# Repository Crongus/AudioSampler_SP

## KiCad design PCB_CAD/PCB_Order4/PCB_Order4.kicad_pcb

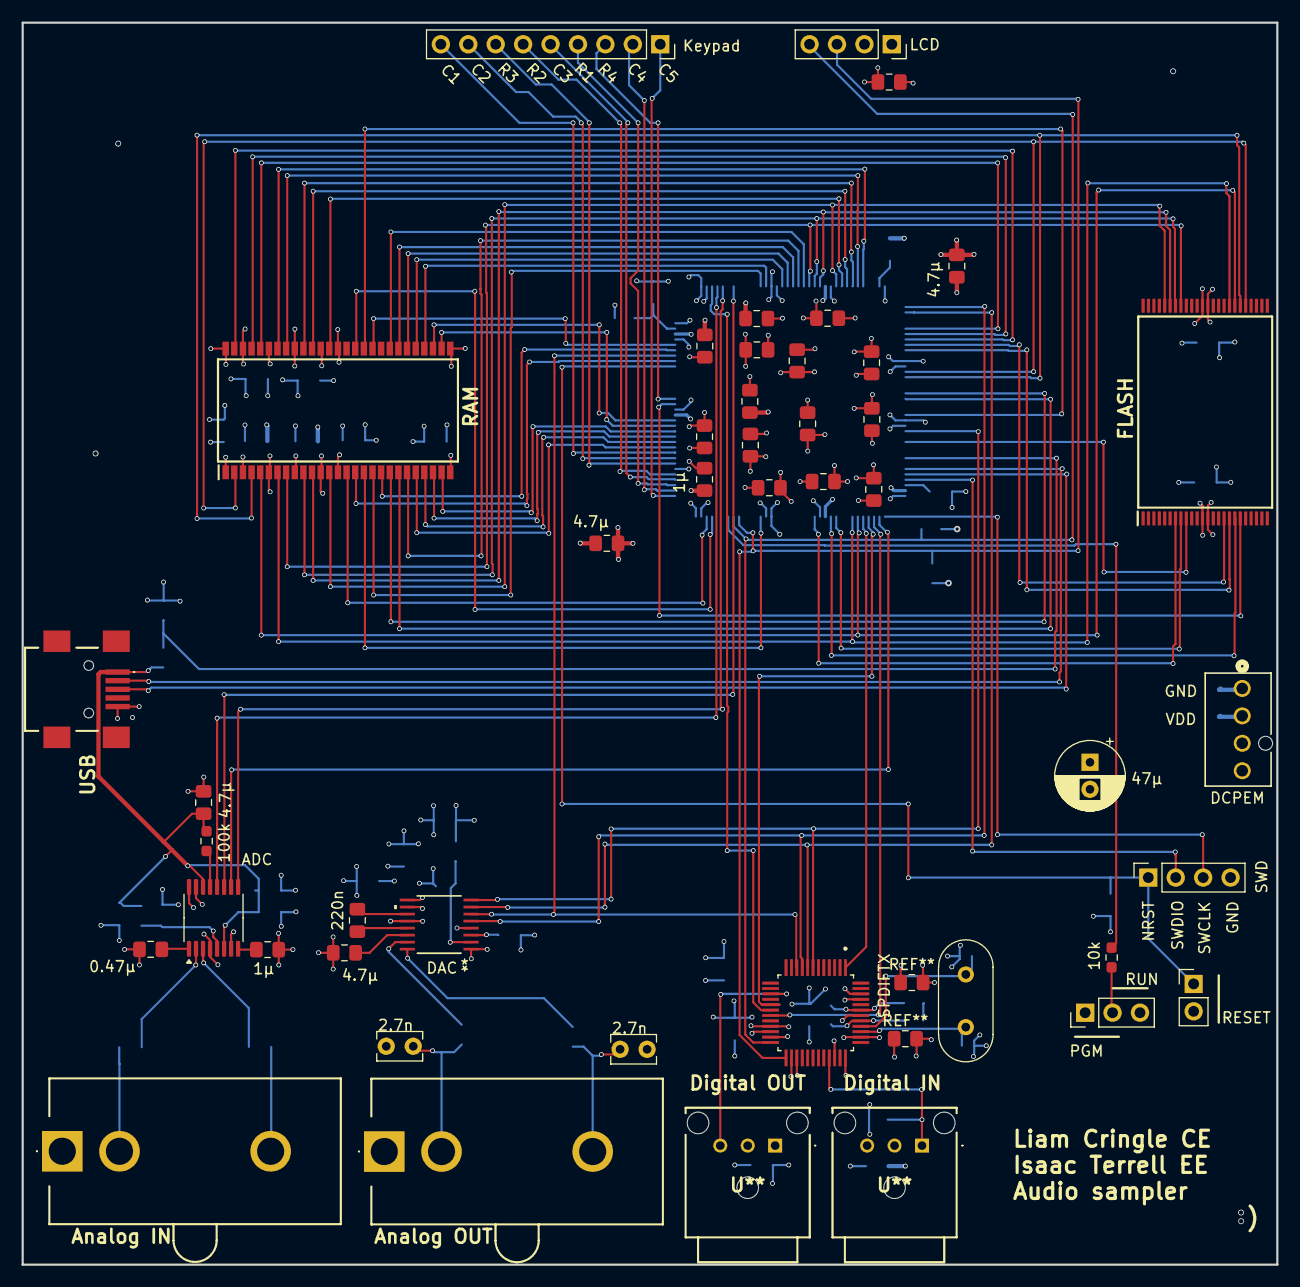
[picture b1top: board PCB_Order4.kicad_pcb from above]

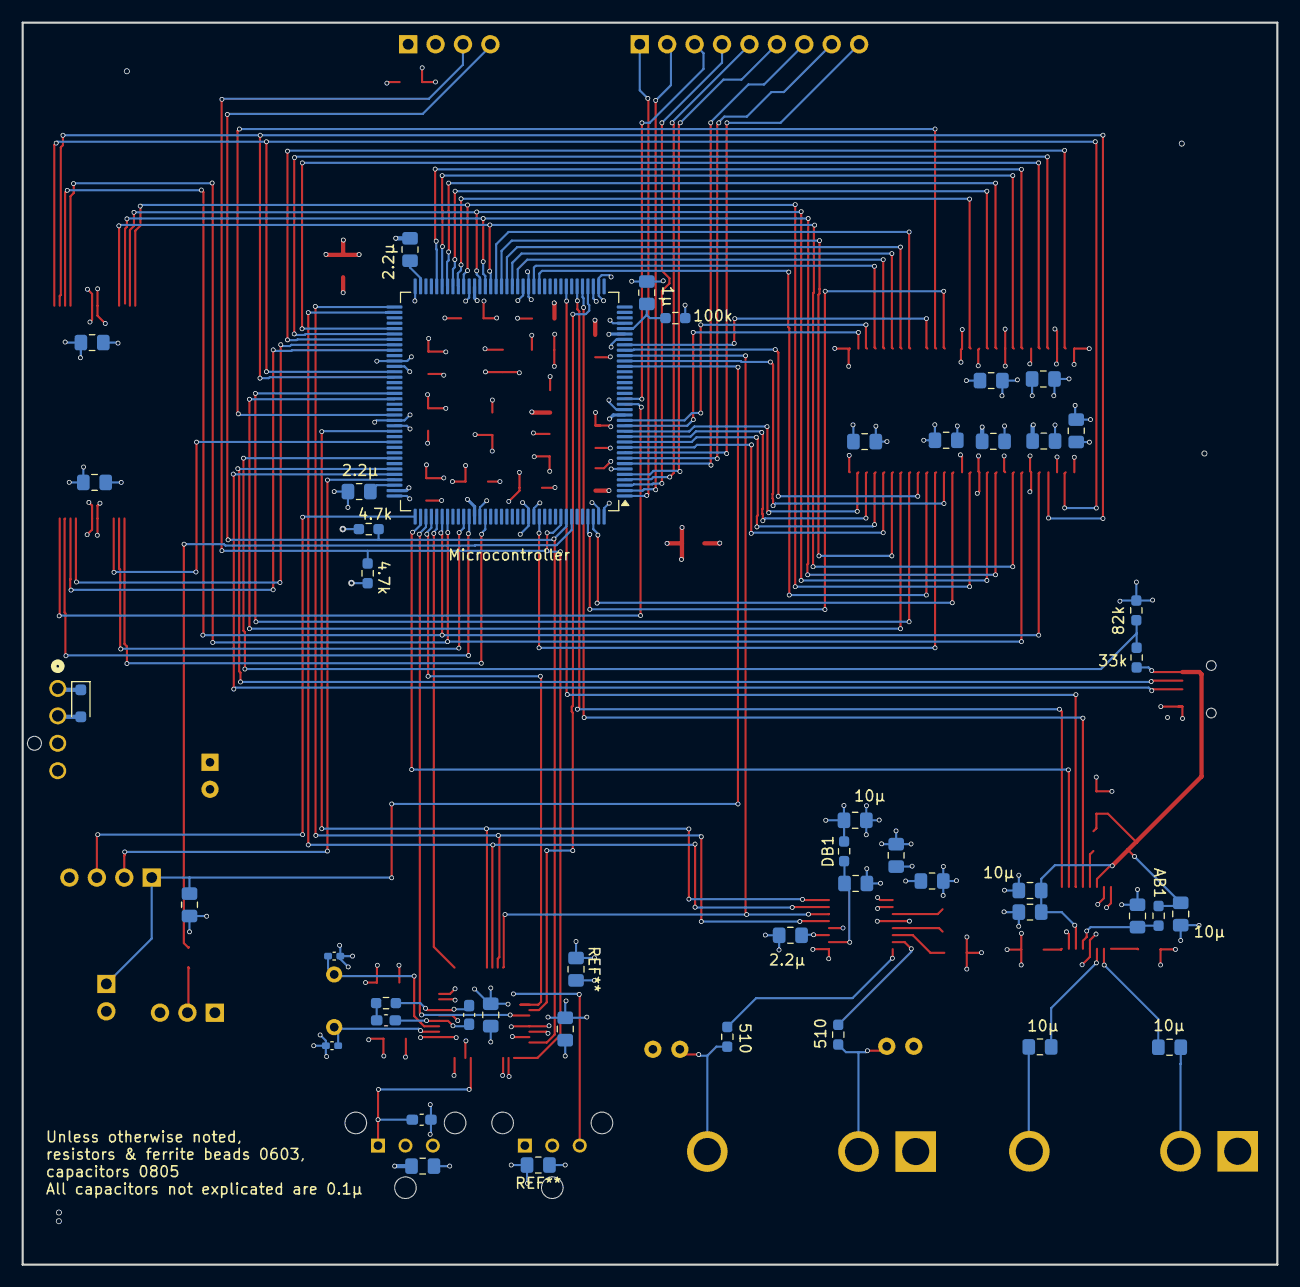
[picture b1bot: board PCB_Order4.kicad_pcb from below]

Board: 4 copper layers, 116.2 x 115.0 mm, 75 parts (32 on the bottom side), 100 nets.

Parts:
AB1: 600; R_0603_1608Metric_Pad0.98x0.95mm_HandSolder
ADC: AK5720VT; TSSOP-16_4.4x5mm_P0.65mm
AR1: 100k; R_0603_1608Metric_Pad0.98x0.95mm_HandSolder
AbC1, AbC2: 10u; C_0805_2012Metric_Pad1.18x1.45mm_HandSolder
AbC3: 4.7u; C_0805_2012Metric_Pad1.18x1.45mm_HandSolder
AcC1: 0.47u; C_0805_2012Metric_Pad1.18x1.45mm_HandSolder
AdbC1, AdbC2: 10u; C_0805_2012Metric_Pad1.18x1.45mm_HandSolder
AnC1, AnC2: 0.1u; C_0805_2012Metric_Pad1.18x1.45mm_HandSolder
Analog IN: FW6190
Analog OUT: FW6190
ArC1: 1u; C_0805_2012Metric_Pad1.18x1.45mm_HandSolder
BC1: 0.1u; C_0805_2012Metric_Pad1.18x1.45mm_HandSolder
DAC: NAU8402WG; TSSOP16_NAU8402_NUV
DB1: 600; R_0603_1608Metric_Pad0.98x0.95mm_HandSolder
DCPEM: 470531000; CONN_SD-47053-001_H10p00_MOL
DacOut_L_decouple1: 2.7n; C_Rect_L4.0mm_W2.5mm_P2.50mm
DacOut_L_res1: 510; R_0603_1608Metric_Pad0.98x0.95mm_HandSolder
DacOut_R_decouple1: 2.7n; C_Rect_L4.0mm_W2.5mm_P2.50mm
DacOut_R_res1: 510; R_0603_1608Metric_Pad0.98x0.95mm_HandSolder
Dac_DigitalSup_noise1, Dac_DigitalSup_noise2: 0.1u; C_0805_2012Metric_Pad1.18x1.45mm_HandSolder
DbC1: 10u; C_0805_2012Metric_Pad1.18x1.45mm_HandSolder
DcC1: 220n; C_0805_2012Metric_Pad1.18x1.45mm_HandSolder
DcC2: 4.7u; C_0805_2012Metric_Pad1.18x1.45mm_HandSolder
DnC1: 0.1u; C_0805_2012Metric_Pad1.18x1.45mm_HandSolder
DrC1: 2.2u; C_0805_2012Metric_Pad1.18x1.45mm_HandSolder
FLASH: TC58BVG1S3HTA00; SOP50P2000X120-48N
FnC1, FnC2: 0.1u; C_0805_2012Metric_Pad1.18x1.45mm_HandSolder
Keypad: PinSocket_1x09_P2.54mm_Vertical
LCD: PinSocket_1x04_P2.54mm_Vertical
LnC1: 0.1u; C_0805_2012Metric_Pad1.18x1.45mm_HandSolder
MR1: 100k; R_0603_1608Metric_Pad0.98x0.95mm_HandSolder
MbC1, MbC2: 4.7u; C_0805_2012Metric_Pad1.18x1.45mm_HandSolder
MbC2#2: 1u; C_0805_2012Metric_Pad1.18x1.45mm_HandSolder
MbC3, MbC4: 2.2u; C_0805_2012Metric_Pad1.18x1.45mm_HandSolder
Microcontroller: STM32H7A3ZITx; LQFP-144_20x20mm_P0.5mm
MnC1, MnC2, MnC3, MnC4, MnC5, MnC6, MnC7, MnC8, MnC9, MnC10, MnC11, MnC12, MnC13: 0.1u; C_0805_2012Metric_Pad1.18x1.45mm_HandSolder
MunC1: 0.1u; C_0805_2012Metric_Pad1.18x1.45mm_HandSolder
MunC2: 1u; C_0805_2012Metric_Pad1.18x1.45mm_HandSolder
PEC3: 47u; CP_Radial_D6.3mm_P2.50mm
RAM: AS4C8M16SA-6TCN; SOP80P1176X120-54N
RESET: PinHeader_1x02_P2.54mm_Vertical
RnC1, RnC2, RnC3, RnC4, RnC5, RnC6, RnC7: 0.1u; C_0805_2012Metric_Pad1.18x1.45mm_HandSolder
SPDIFTX: DIX9211PTR
SR1: 10k; R_0603_1608Metric_Pad0.98x0.95mm_HandSolder
SWD: Conn_01x03_Socket; PinSocket_1x04_P2.54mm_Vertical
U**: FCR684216R
U**#2: FCR684216T
UR1: 33k; R_0603_1608Metric_Pad0.98x0.95mm_HandSolder
UR2: 82k; R_0603_1608Metric_Pad0.98x0.95mm_HandSolder
USB: USB-M26FTR; USBM26FTR

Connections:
/BOOTSW: Microcontroller.138 (BOOT0), SR1.2
/DEBUG_SWCLK: Microcontroller.109 (PA14), SWD.3
/DEBUG_SWDIO: Microcontroller.105 (PA13), SWD.2
/FMC_A0: Microcontroller.10 (PF0), RAM.23 (A0)
/FMC_A1: Microcontroller.11 (PF1), RAM.24 (A1)
/FMC_A2: Microcontroller.12 (PF2), RAM.25 (A2)
/FMC_A3: Microcontroller.13 (PF3), RAM.26 (A3)
/FMC_A4: Microcontroller.14 (PF4), RAM.29 (A4)
/FMC_A5: Microcontroller.15 (PF5), RAM.30 (A5)
/FMC_A6: Microcontroller.50 (PF12), RAM.31 (A6)
/FMC_A7: Microcontroller.53 (PF13), RAM.32 (A7)
/FMC_A8: Microcontroller.54 (PF14), RAM.33 (A8)
/FMC_A9: Microcontroller.55 (PF15), RAM.34 (A9)
/FMC_A10: Microcontroller.56 (PG0), RAM.22 (A10/AP)
/FMC_A11: Microcontroller.57 (PG1), RAM.35 (A11)
/FMC_ALE: FLASH.17 (ALE), Microcontroller.81 (PD12)
/FMC_BA0: Microcontroller.89 (PG4), RAM.20 (BA0)
/FMC_BA1: Microcontroller.90 (PG5), RAM.21 (BA1)
/FMC_CLE: FLASH.16 (CLE), Microcontroller.80 (PD11)
/FMC_D0: FLASH.29 (I/O1), Microcontroller.85 (PD14), RAM.2 (DQ0)
/FMC_D1: FLASH.30 (I/O2), Microcontroller.86 (PD15), RAM.4 (DQ1)
/FMC_D2: FLASH.31 (I/O3), Microcontroller.114 (PD0), RAM.5 (DQ2)
/FMC_D3: FLASH.32 (I/O4), Microcontroller.115 (PD1), RAM.7 (DQ3)
/FMC_D4: FLASH.41 (I/O5), Microcontroller.58 (PE7), RAM.8 (DQ4)
/FMC_D5: FLASH.42 (I/O6), Microcontroller.59 (PE8), RAM.10 (DQ5)
/FMC_D6: FLASH.43 (I/O7), Microcontroller.60 (PE9), RAM.11 (DQ6)
/FMC_D7: FLASH.44 (I/O8), Microcontroller.63 (PE10), RAM.13 (DQ7)
/FMC_D8: Microcontroller.64 (PE11), RAM.42 (DQ8)
/FMC_D9: Microcontroller.65 (PE12), RAM.44 (DQ9)
/FMC_D10: Microcontroller.66 (PE13), RAM.45 (DQ10)
/FMC_D11: Microcontroller.67 (PE14), RAM.47 (DQ11)
/FMC_D12: Microcontroller.68 (PE15), RAM.48 (DQ12)
/FMC_D13: Microcontroller.77 (PD8), RAM.50 (DQ13)
/FMC_D14: Microcontroller.78 (PD9), RAM.51 (DQ14)
/FMC_D15: Microcontroller.79 (PD10), RAM.53 (DQ15)
/FMC_NBL0: Microcontroller.141 (PE0), RAM.39 (UDQM)
/FMC_NBL1: Microcontroller.142 (PE1), RAM.15 (LDQM)
/FMC_NCE: FLASH.9 (~CE), Microcontroller.98 (PC8)
/FMC_NOE: FLASH.8 (~RE), Microcontroller.118 (PD4)
/FMC_NWAIT: FLASH.7 (RY/~BY), Microcontroller.122 (PD6)
/FMC_NWE: FLASH.18 (~WE), Microcontroller.119 (PD5)
/FMC_SDCKE0: Microcontroller.29 (PC3_C), RAM.37 (CKE)
/FMC_SDCLK: Microcontroller.93 (PG8), RAM.38 (CLK)
/FMC_SDNCAS: Microcontroller.132 (PG15), RAM.17 (CAS#)
/FMC_SDNE0: Microcontroller.28 (PC2_C), RAM.19 (CS#)
/FMC_SDNRAS: Microcontroller.49 (PF11), RAM.18 (RAS#)
/FMC_SDNWE: Microcontroller.26 (PC0), RAM.16 (WE#)
/Flash_WP: FLASH.19 (~WP), Microcontroller.18 (PF6)
/I2C1_SCL: LCD.3 (SCL), Microcontroller.136 (PB6), SPDIFTX.25 (MC/SCL)
/I2C1_SDA: LCD.4 (SDA), Microcontroller.137 (PB7), SPDIFTX.24 (MDI/SDA)
/I2S1_CK: ADC.12 (BICK), Microcontroller.41 (PA5)
/I2S1_MCK: ADC.11 (MCLK), Microcontroller.44 (PC4)
/I2S1_SDI: ADC.9 (SDTO), Microcontroller.42 (PA6)
/I2S1_WS: ADC.10 (LRCLK), Microcontroller.110 (PA15)
/I2S2_CK: DAC.7 (BCLK), Microcontroller.74 (PB13), SPDIFTX.8 (MPIO_C1)
/I2S2_MCK: DAC.8 (MCLK), Microcontroller.96 (PC6), SPDIFTX.7 (MPIO_C0)
/I2S2_SDO: DAC.6 (DACIN), Microcontroller.27 (PC1), SPDIFTX.10 (MPIO_C3)
/I2S2_WS: DAC.5 (FS), Microcontroller.73 (PB12), SPDIFTX.9 (MPIO_C2)
/KP_Col1: Keypad.9, Microcontroller.9 (PC15)
/KP_Col2: Keypad.8 (N), Microcontroller.8 (PC14)
/KP_Col3: Keypad.5 (K), Microcontroller.4 (PE5)
/KP_Col4: Keypad.2 (G), Microcontroller.2 (PE3)
/KP_Col5: Keypad.1 (F), Microcontroller.1 (PE2)
/KP_Row1: Keypad.4 (J), Microcontroller.3 (PE4)
/KP_Row2: Keypad.6 (L), Microcontroller.5 (PE6)
/KP_Row3: Keypad.7 (M), Microcontroller.7 (PC13)
/KP_Row4: Keypad.3 (H), Microcontroller.19 (PF7)
/RST_BTN: BC1.1, Microcontroller.25 (NRST), RESET.1, SWD.1
/SPDIFRX_IN0: SPDIFTX.33 (RXIN2), U**.1
/SPDIFTX_OUT: SPDIFTX.15 (MPO0), U**#2.3
/USB_OTG_HS_DM: Microcontroller.103 (PA11), USB.2
/USB_OTG_HS_DP: Microcontroller.104 (PA12), USB.3
/USB_OTG_HS_VBUS: Microcontroller.101 (PA9), UR1.1, UR2.2
GNDD: ADC.4 (VSS), ADC.7 (GSEL), ADC.15 (FSEL), ADC.16 (CKS), AbC1.2, AbC2.2, AbC3.2, AcC1.2, AnC1.1, AnC2.2, Analog IN.1, Analog OUT.1, ArC1.2, BC1.2, DAC.1 (VSSA), DAC.12 (LINEGND), DCPEM.1, DacOut_L_decouple1.2, DacOut_R_decouple1.2, Dac_DigitalSup_noise1.2, Dac_DigitalSup_noise2.2, DbC1.2, DcC2.2, DnC1.1, DrC1.1, FLASH.13 (VSS_1), FLASH.36 (VSS_2), FnC1.1, FnC2.1, LCD.2 (GND), LnC1.1, MbC1.2, MbC2.2, MbC2#2.2, MbC3.2, MbC4.2, Microcontroller.16 (VSS), Microcontroller.31 (VSSA), Microcontroller.38 (VSS), Microcontroller.51 (VSS), Microcontroller.61 (VSS), Microcontroller.83 (VSS), Microcontroller.94 (VSS), Microcontroller.107 (VSS), Microcontroller.120 (VSS), Microcontroller.130 (VSS), MnC1.2, MnC2.2, MnC3.2, MnC4.2, MnC5.2, MnC6.2, MnC7.2, MnC8.2, MnC9.2, MnC10.2, MnC11.1, MnC12.2, MnC13.2, MunC1.2, MunC2.2, PEC3.2, RAM.6 (VSSQ_1), RAM.12 (VSSQ_2), RAM.28 (VSS_1), RAM.41 (VSS_2), RAM.46 (VSSQ_3), RAM.52 (VSSQ_4), RAM.54 (VSS_3), RESET.2, RnC1.2, RnC2.1, RnC3.1, RnC4.1, RnC5.2, RnC6.1, RnC7.1, SPDIFTX.21 (DGND), SPDIFTX.23 (MDO/ADR0), SPDIFTX.26 (MS/ADR1), SPDIFTX.27 (MODE), SPDIFTX.38 (GNDRX), SPDIFTX.41 (AGND), SPDIFTX.45 (RSV1), SPDIFTX.46 (RSV1), SWD.4, U**.2, U**#2.1, UR2.1, USB.5
I2S3_BCK: Microcontroller.111 (PC10), SPDIFTX.19 (BCK)
I2S3_DIN: Microcontroller.112 (PC11), SPDIFTX.17 (DOUT)
I2S3_LRCK: Microcontroller.40 (PA4), SPDIFTX.18 (LRCK)
unnamed: ADC.3 (LIN), AdbC2.2
unnamed: ADC.8 (REGO), ArC1.1
unnamed: ADC.2 (RIN), AdbC1.2
unnamed: AB1.2, ADC.5 (VA), AnC1.2
unnamed: ADC.1 (VCOM), AcC1.1
unnamed: ADC.13 (~PDN), AR1.1
unnamed: AdbC1.1, Analog IN.2
unnamed: AdbC2.1, Analog IN.3
unnamed: DAC.11 (CPCA), DcC1.2
unnamed: DAC.13 (CPCB), DcC1.1
unnamed: DAC.14 (CPOUT), DcC2.1
unnamed: DAC.16 (LLINEOU), DacOut_L_res1.1
unnamed: DAC.15 (RLINEOUT), DacOut_R_res1.1
unnamed: DAC.2 (VDDA), DB1.2, DnC1.2
unnamed: DAC.3 (VREF), DrC1.2
unnamed: Analog OUT.3, DacOut_L_decouple1.1, DacOut_L_res1.2
unnamed: Analog OUT.2, DacOut_R_decouple1.1, DacOut_R_res1.2
unnamed: MbC3.1, Microcontroller.71 (VCAP)
unnamed: MbC4.1, Microcontroller.106 (VCAP)
unnamed: MR1.2, MbC2#2.1, Microcontroller.32 (VREF+)
SPDIF_ERR: Microcontroller.113 (PC12), SPDIFTX.1 (ERROR/INT0)
VDD: DAC.4 (MUTEB), DAC.9 (VDDB), DAC.10 (LINEVDD), DB1.1, DCPEM.2, Dac_DigitalSup_noise1.1, Dac_DigitalSup_noise2.1, DbC1.1, FLASH.12 (VCC_1), FLASH.37 (VCC_2), FnC1.2, FnC2.2, LCD.1 (VCC), LnC1.2, MR1.1, MbC1.1, MbC2.1, Microcontroller.6 (VBAT), Microcontroller.17 (VDD), Microcontroller.30 (VDD), Microcontroller.33 (VDDA), Microcontroller.39 (VDD), Microcontroller.52 (VDD), Microcontroller.62 (VDD), Microcontroller.72 (VDD), Microcontroller.84 (VDD), Microcontroller.95 (VDD33_USB), Microcontroller.108 (VDD), Microcontroller.121 (VDDMMC), Microcontroller.131 (VDD), Microcontroller.143 (PDR_ON), Microcontroller.144 (VDD), MnC1.1, MnC2.1, MnC3.1, MnC4.1, MnC5.1, MnC6.1, MnC7.1, MnC8.1, MnC9.1, MnC10.1, MnC11.2, MnC12.1, MnC13.1, MunC1.1, MunC2.1, PEC3.1, RAM.1 (VDD_1), RAM.3 (VDDQ_1), RAM.9 (VDDQ_2), RAM.14 (VDD_2), RAM.27 (VDD_3), RAM.43 (VDDQ_3), RAM.49 (VDDQ_4), RnC1.1, RnC2.2, RnC3.2, RnC4.2, RnC5.1, RnC6.2, RnC7.2, SPDIFTX.22 (DVDD), SPDIFTX.34 (RST), SPDIFTX.36 (VDDRX), SPDIFTX.42 (VCC), U**.3, U**#2.2
VUSB: AB1.1, ADC.6 (VD), ADC.14 (DIF/TDMI), AR1.2, AbC1.1, AbC2.1, AbC3.1, AnC2.1, UR1.2, USB.1

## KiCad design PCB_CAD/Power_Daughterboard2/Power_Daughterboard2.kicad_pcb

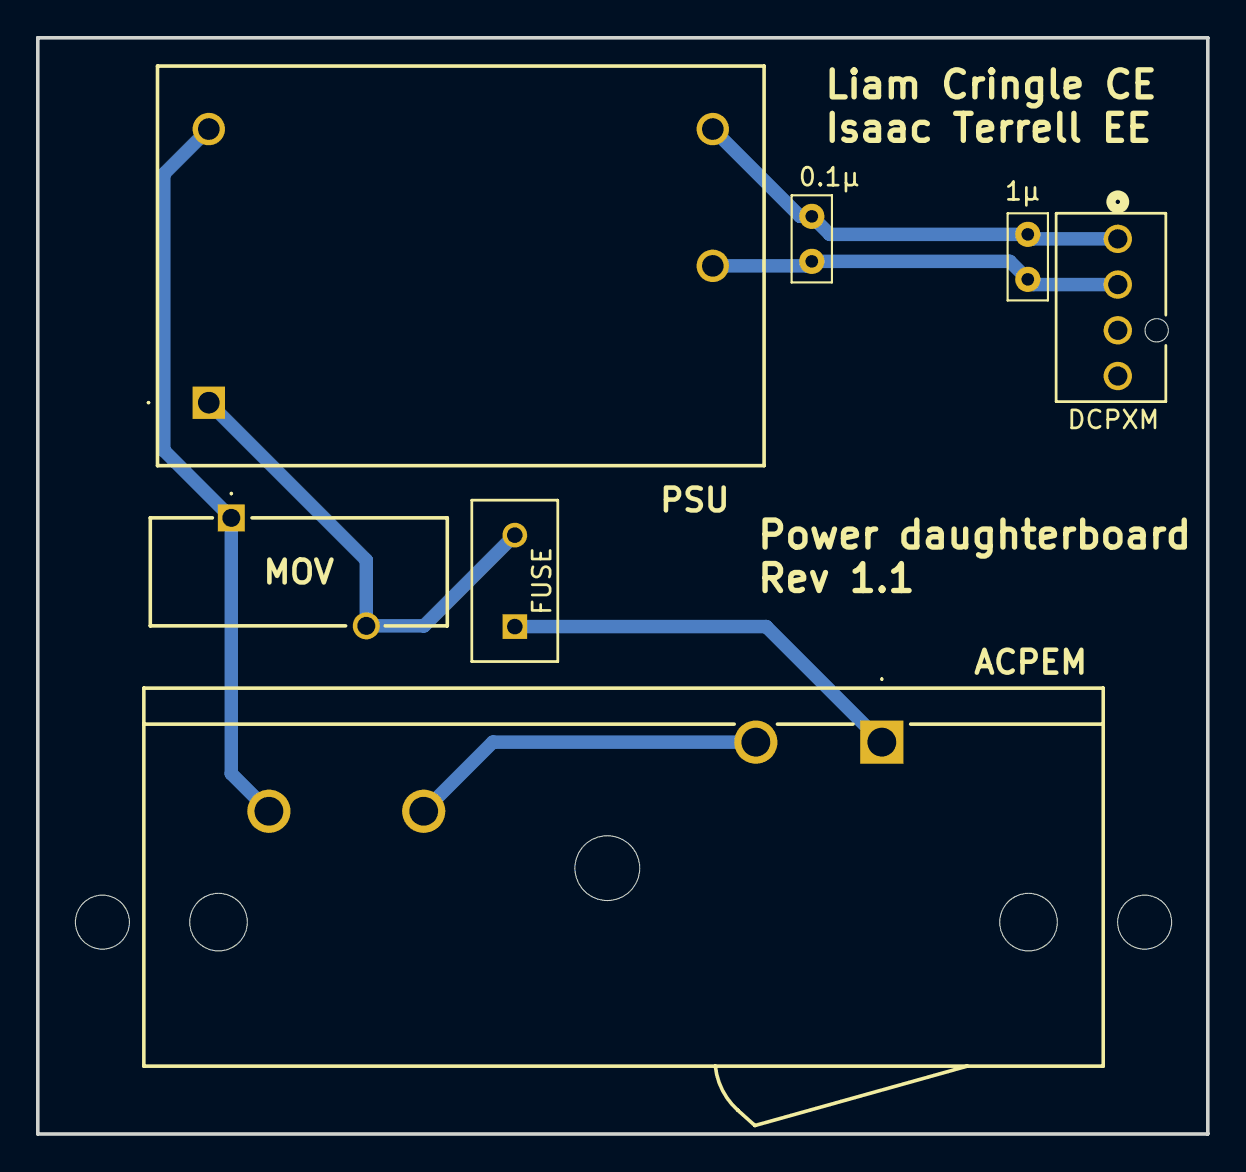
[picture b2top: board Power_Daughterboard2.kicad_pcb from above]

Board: 2 copper layers, 65.0 x 60.9 mm, 7 parts (0 on the bottom side), 6 nets.

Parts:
ACPEM: CMF2113112
C1: 0.1u; C_Rect_L4.6mm_W2.0mm_P2.50mm_MKS02_FKP02
C2: 1u; C_Rect_L4.6mm_W2.0mm_P2.50mm_MKS02_FKP02
DCPXM: 470531000; CONN_SD-47053-001_H10p00_MOL
FUSE: SS-5H-1A-APH; FUSE_SS-5H-1A_EAT
MOV: MOV-14D561KTR; MOV14D561KTR
PSU: HP02S0300WI

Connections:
unnamed: ACPEM.1, FUSE.1
unnamed: ACPEM.2, ACPEM.L1
unnamed: FUSE.2, MOV.2, PSU.1 (AC1)
unnamed: ACPEM.N1, MOV.1, PSU.2 (AC2)
unnamed: C1.1, C2.1, DCPXM.2, PSU.4 (DC+)
unnamed: C1.2, C2.2, DCPXM.1, PSU.3 (DC-)

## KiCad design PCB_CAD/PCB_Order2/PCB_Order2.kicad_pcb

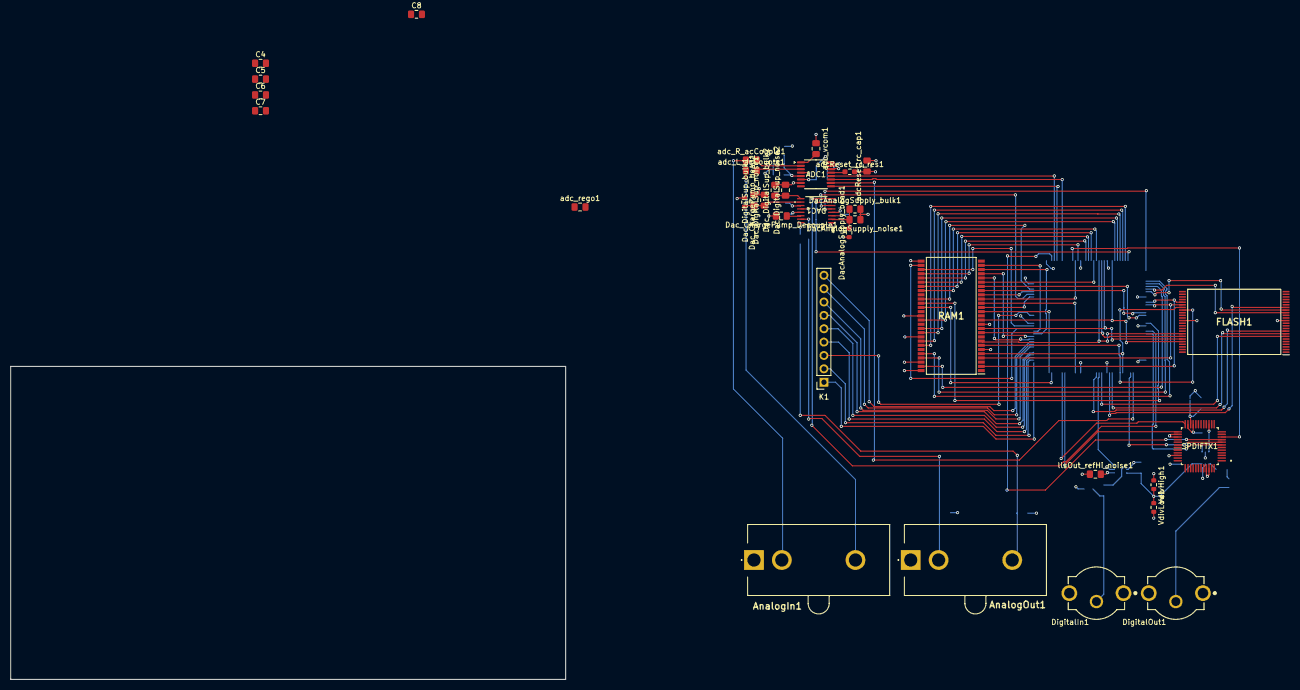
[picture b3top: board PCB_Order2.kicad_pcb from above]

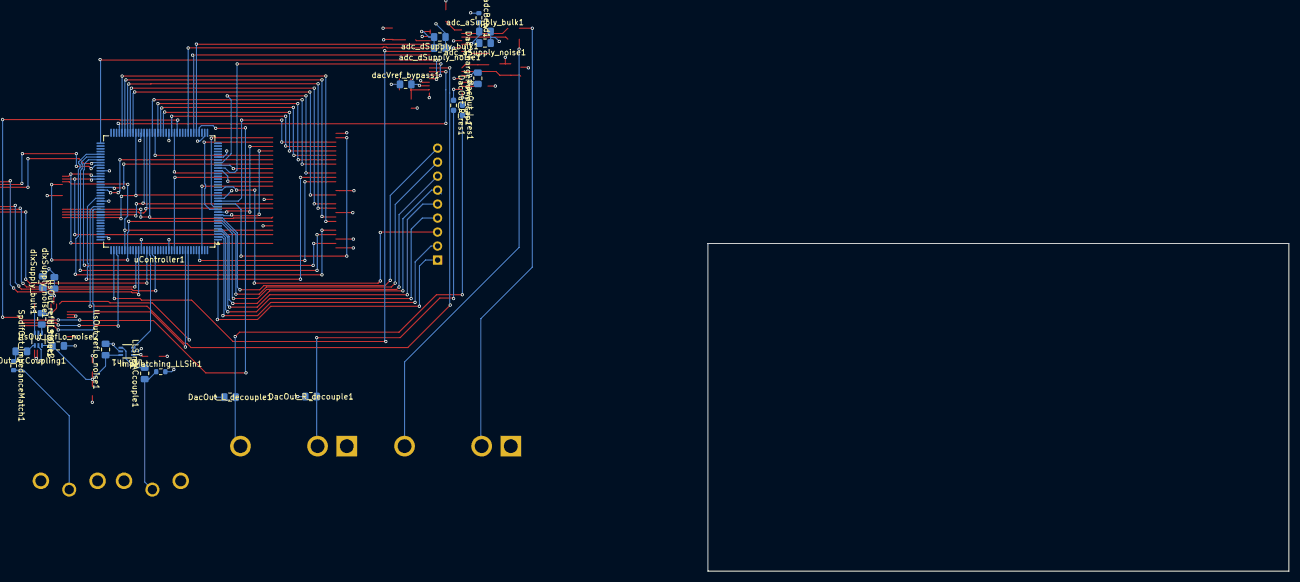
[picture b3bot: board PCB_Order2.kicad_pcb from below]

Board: 4 copper layers, 105.5 x 59.5 mm, 56 parts (23 on the bottom side), 99 nets.

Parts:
ADC1: AK5720VT; TSSOP-16_4.4x5mm_P0.65mm
AnalogIn1: FW6190
AnalogOut1: FW6190
C4, C6: 10uF; C_0805_2012Metric_Pad1.18x1.45mm_HandSolder
C5, C7: 0.1uF; C_0805_2012Metric_Pad1.18x1.45mm_HandSolder
C8: 1uF; C_0805_2012Metric_Pad1.18x1.45mm_HandSolder
DAC1: NAU8402WG; TSSOP16_NAU8402_NUV
DacAnalogSupply_bead1: *TBD*; R_0603_1608Metric
DacAnalogSupply_bulk1: 15u; C_0805_2012Metric_Pad1.18x1.45mm_HandSolder
DacAnalogSupply_noise1: 0.15u; C_0805_2012Metric_Pad1.18x1.45mm_HandSolder
DacOut_L_decouple1: 2.7n; C_0805_2012Metric_Pad1.18x1.45mm_HandSolder
DacOut_L_res1: 500; R_0603_1608Metric_Pad0.98x0.95mm_HandSolder
DacOut_R_decouple1: 2.7n; C_0805_2012Metric_Pad1.18x1.45mm_HandSolder
DacOut_R_res1: 500; R_0603_1608Metric_Pad0.98x0.95mm_HandSolder
Dac_ChargePump_Decouple1: 4.7uF; C_0805_2012Metric_Pad1.18x1.45mm_HandSolder
Dac_ChargePump_bead1: 600; R_0603_1608Metric
Dac_ChargePump_cap1: 220nF; C_0805_2012Metric_Pad1.18x1.45mm_HandSolder
Dac_DigitalSup_bulk1, Dac_DigitalSup_bulk2: 15u; C_0805_2012Metric_Pad1.18x1.45mm_HandSolder
Dac_DigitalSup_noise1, Dac_DigitalSup_noise2: 0.15u; C_0805_2012Metric_Pad1.18x1.45mm_HandSolder
DigitalIn1: RCJ-027; CUI_RCJ-027
DigitalOut1: RCJ-027; CUI_RCJ-027
FLASH1: TC58BVG1S3HTA00; SOP50P2000X120-48N
ImpMatching_LLSin1: 75; R_0603_1608Metric
K1: PinSocket_1x09_P2.54mm_Vertical
LLS In1: SN74AXCH1T45DCKR; DCK6_TEX
LLS Out1: SN74AXCH1T45DCKR; DCK6_TEX
LLSin_ACcouple1: 0.1u; C_0805_2012Metric_Pad1.18x1.45mm_HandSolder
RAM1: AS4C8M16SA-6TCN; SOP80P1176X120-54N
SPDIFTX1: DIX9211PTR
SpdifOut_AcCoupling1: 0.1u; C_0805_2012Metric_Pad1.18x1.45mm_HandSolder
SpdifOut_ImpedanceMatch1: 75; R_0603_1608Metric
VdivHigh1: 8.87k; R_0603_1608Metric
VdivLow1: 2.21k; R_0603_1608Metric
adcBead1: 600; R_0603_1608Metric
adcReset_rc_cap1: 47u; C_0805_2012Metric_Pad1.18x1.45mm_HandSolder
adcReset_rc_res1: 100k; R_0603_1608Metric_Pad0.98x0.95mm_HandSolder
adc_L_acCouple1: 10u; C_0805_2012Metric_Pad1.18x1.45mm_HandSolder
adc_R_acCouple1: 10u; C_0805_2012Metric_Pad1.18x1.45mm_HandSolder
adc_aSupply_bulk1: 15u; C_0805_2012Metric_Pad1.18x1.45mm_HandSolder
adc_aSupply_noise1: 0.15u; C_0805_2012Metric_Pad1.18x1.45mm_HandSolder
adc_dSupply_bulk1: 15u; C_0805_2012Metric_Pad1.18x1.45mm_HandSolder
adc_dSupply_noise1: 0.15u; C_0805_2012Metric_Pad1.18x1.45mm_HandSolder
adc_rego1: 1u; C_0805_2012Metric_Pad1.18x1.45mm_HandSolder
adc_vcom1: 0.47u; C_0805_2012Metric_Pad1.18x1.45mm_HandSolder
dacVref_bypass1: 2.2uF; C_0805_2012Metric_Pad1.18x1.45mm_HandSolder
dixSupply_bulk1: 15u; C_0805_2012Metric_Pad1.18x1.45mm_HandSolder
dixSupply_noise1: 0.15u; C_0805_2012Metric_Pad1.18x1.45mm_HandSolder
llsOut_refHi_noise1, llsOut_refHi_noise2: 0.15u; C_0805_2012Metric_Pad1.18x1.45mm_HandSolder
llsOut_refLo_noise1, llsOut_refLo_noise2: 0.15u; C_0805_2012Metric_Pad1.18x1.45mm_HandSolder
uController1: STM32H7A3ZITx; LQFP-144_20x20mm_P0.5mm

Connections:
/FMC_A0: RAM1.23 (A0), uController1.10 (PF0)
/FMC_A1: RAM1.24 (A1), uController1.11 (PF1)
/FMC_A2: RAM1.25 (A2), uController1.12 (PF2)
/FMC_A3: RAM1.26 (A3), uController1.13 (PF3)
/FMC_A4: RAM1.29 (A4), uController1.14 (PF4)
/FMC_A5: RAM1.30 (A5), uController1.15 (PF5)
/FMC_A6: RAM1.31 (A6), uController1.50 (PF12)
/FMC_A7: RAM1.32 (A7), uController1.53 (PF13)
/FMC_A8: RAM1.33 (A8), uController1.54 (PF14)
/FMC_A9: RAM1.34 (A9), uController1.55 (PF15)
/FMC_A10: RAM1.22 (A10/AP), uController1.56 (PG0)
/FMC_A11: RAM1.35 (A11), uController1.57 (PG1)
/FMC_ALE: FLASH1.17 (ALE), uController1.81 (PD12)
/FMC_BA0: RAM1.20 (BA0), uController1.89 (PG4)
/FMC_BA1: RAM1.21 (BA1), uController1.90 (PG5)
/FMC_CLE: FLASH1.16 (CLE), uController1.80 (PD11)
/FMC_D0: FLASH1.29 (I/O1), RAM1.2 (DQ0), uController1.85 (PD14)
/FMC_D1: FLASH1.30 (I/O2), RAM1.4 (DQ1), uController1.86 (PD15)
/FMC_D2: FLASH1.31 (I/O3), RAM1.5 (DQ2), uController1.114 (PD0)
/FMC_D3: FLASH1.32 (I/O4), RAM1.7 (DQ3), uController1.115 (PD1)
/FMC_D4: FLASH1.41 (I/O5), RAM1.8 (DQ4), uController1.58 (PE7)
/FMC_D5: FLASH1.42 (I/O6), RAM1.10 (DQ5), uController1.59 (PE8)
/FMC_D6: FLASH1.43 (I/O7), RAM1.11 (DQ6), uController1.60 (PE9)
/FMC_D7: FLASH1.44 (I/O8), RAM1.13 (DQ7), uController1.63 (PE10)
/FMC_D8: RAM1.42 (DQ8), uController1.64 (PE11)
/FMC_D9: RAM1.44 (DQ9), uController1.65 (PE12)
/FMC_D10: RAM1.45 (DQ10), uController1.66 (PE13)
/FMC_D11: RAM1.47 (DQ11), uController1.67 (PE14)
/FMC_D12: RAM1.48 (DQ12), uController1.68 (PE15)
/FMC_D13: RAM1.50 (DQ13), uController1.77 (PD8)
/FMC_D14: RAM1.51 (DQ14), uController1.78 (PD9)
/FMC_D15: RAM1.53 (DQ15), uController1.79 (PD10)
/FMC_NBL0: RAM1.39 (UDQM), uController1.141 (PE0)
/FMC_NBL1: RAM1.15 (LDQM), uController1.142 (PE1)
/FMC_NCE: FLASH1.9 (~CE), uController1.124 (PG9)
/FMC_NOE: FLASH1.8 (~RE), uController1.118 (PD4)
/FMC_NWAIT: FLASH1.7 (RY/~BY), uController1.122 (PD6)
/FMC_NWE: FLASH1.18 (~WE), uController1.119 (PD5)
/FMC_SDCKE0: RAM1.37 (CKE), uController1.29 (PC3_C)
/FMC_SDCLK: RAM1.38 (CLK), uController1.93 (PG8)
/FMC_SDNCAS: RAM1.17 (CAS#), uController1.132 (PG15)
/FMC_SDNE0: RAM1.19 (CS#), uController1.28 (PC2_C)
/FMC_SDNRAS: RAM1.18 (RAS#), uController1.49 (PF11)
/FMC_SDNWE: RAM1.16 (WE#), uController1.26 (PC0)
/Flash_WP: FLASH1.19 (~WP), uController1.18 (PF6)
/I2C1_SCL: SPDIFTX1.25 (MC/SCL), uController1.136 (PB6)
/I2C1_SDA: SPDIFTX1.24 (MDI/SDA), uController1.137 (PB7)
/I2S1_CK: ADC1.12 (BICK), uController1.41 (PA5)
/I2S1_MCK: ADC1.11 (MCLK), uController1.44 (PC4)
/I2S1_SDI: ADC1.9 (SDTO), uController1.42 (PA6)
/I2S1_WS: ADC1.10 (LRCLK), uController1.110 (PA15)
/I2S2_CK: DAC1.7 (BCLK), uController1.69 (PB10)
/I2S2_MCK: DAC1.8 (MCLK), uController1.96 (PC6)
/I2S2_SDO: DAC1.6 (DACIN), uController1.27 (PC1)
/I2S2_WS: DAC1.5 (FS), uController1.73 (PB12)
/I2S3_CK: SPDIFTX1.8 (MPIO_C1), uController1.111 (PC10)
/I2S3_MCK: SPDIFTX1.7 (MPIO_C0), uController1.97 (PC7)
/I2S3_SDO: SPDIFTX1.10 (MPIO_C3), uController1.48 (PB2)
/I2S3_WS: SPDIFTX1.9 (MPIO_C2), uController1.40 (PA4)
/KP_Col1: K1.9, uController1.9 (PC15)
/KP_Col2: K1.8 (N), uController1.8 (PC14)
/KP_Col3: K1.5 (K), uController1.4 (PE5)
/KP_Col4: K1.2 (G), uController1.2 (PE3)
/KP_Col5: K1.1 (F), uController1.1 (PE2)
/KP_Row1: K1.4 (J), uController1.3 (PE4)
/KP_Row2: K1.6 (L), uController1.5 (PE6)
/KP_Row3: K1.7 (M), uController1.7 (PC13)
/KP_Row4: K1.3 (H), uController1.19 (PF7)
/SPDIFRX_IN0: LLS In1.3 (A), uController1.123 (PD7)
/SPDIFTX_OUT: LLS Out1.3 (A), SPDIFTX1.15 (MPO0)
GNDA: ADC1.4 (VSS), AnalogIn1.1, AnalogOut1.1, C4.2, C5.1, DAC1.1 (VSSA), DAC1.12 (LINEGND), uController1.31 (VSSA)
GNDD: ADC1.7 (GSEL), ADC1.15 (FSEL), ADC1.16 (CKS), C6.2, C7.1, C8.2, DacAnalogSupply_bulk1.2, DacAnalogSupply_noise1.1, DacOut_L_decouple1.2, DacOut_R_decouple1.2, Dac_ChargePump_Decouple1.2, Dac_DigitalSup_bulk1.2, Dac_DigitalSup_bulk2.2, Dac_DigitalSup_noise1.2, Dac_DigitalSup_noise2.2, DigitalIn1.1A (1), DigitalOut1.1A (1), FLASH1.13 (VSS_1), FLASH1.36 (VSS_2), ImpMatching_LLSin1.2, LLS In1.2 (GND), LLS In1.5 (DIR), LLS Out1.2 (GND), RAM1.6 (VSSQ_1), RAM1.12 (VSSQ_2), RAM1.28 (VSS_1), RAM1.41 (VSS_2), RAM1.46 (VSSQ_3), RAM1.52 (VSSQ_4), RAM1.54 (VSS_3), SPDIFTX1.21 (DGND), SPDIFTX1.23 (MDO/ADR0), SPDIFTX1.26 (MS/ADR1), SPDIFTX1.27 (MODE), SPDIFTX1.45 (RSV1), SPDIFTX1.46 (RSV1), VdivLow1.2, adcReset_rc_cap1.2, adc_aSupply_bulk1.2, adc_aSupply_noise1.1, adc_dSupply_bulk1.2, adc_dSupply_noise1.2, adc_rego1.2, adc_vcom1.1, dacVref_bypass1.1, dixSupply_bulk1.2, dixSupply_noise1.2, llsOut_refHi_noise1.1, llsOut_refHi_noise2.1, llsOut_refLo_noise1.2, llsOut_refLo_noise2.2, uController1.16 (VSS), uController1.38 (VSS), uController1.51 (VSS), uController1.61 (VSS), uController1.83 (VSS), uController1.94 (VSS), uController1.107 (VSS), uController1.120 (VSS), uController1.130 (VSS)
unnamed: ADC1.3 (LIN), adc_L_acCouple1.2
unnamed: ADC1.8 (REGO), C8.1, adc_rego1.1
unnamed: ADC1.2 (RIN), adc_R_acCouple1.2
unnamed: ADC1.5 (VA), adcBead1.2, adc_aSupply_bulk1.1, adc_aSupply_noise1.2
unnamed: ADC1.1 (VCOM), adc_vcom1.2
unnamed: ADC1.13 (~PDN), adcReset_rc_res1.1
unnamed: AnalogIn1.2, adc_R_acCouple1.1
unnamed: AnalogIn1.3, adc_L_acCouple1.1
unnamed: AnalogOut1.2, DacOut_R_decouple1.1, DacOut_R_res1.2
unnamed: AnalogOut1.3, DacOut_L_decouple1.1, DacOut_L_res1.2
unnamed: DAC1.11 (CPCA), Dac_ChargePump_cap1.2
unnamed: DAC1.13 (CPCB), Dac_ChargePump_cap1.1
unnamed: DAC1.14 (CPOUT), Dac_ChargePump_Decouple1.1
unnamed: DAC1.10 (LINEVDD), Dac_ChargePump_bead1.2, Dac_DigitalSup_bulk1.1, Dac_DigitalSup_noise1.1
unnamed: DAC1.16 (LLINEOU), DacOut_L_res1.1
unnamed: DAC1.15 (RLINEOUT), DacOut_R_res1.1
unnamed: DAC1.2 (VDDA), DacAnalogSupply_bead1.2, DacAnalogSupply_bulk1.1, DacAnalogSupply_noise1.2
unnamed: DAC1.3 (VREF), dacVref_bypass1.2
unnamed: DigitalIn1.2, ImpMatching_LLSin1.1, LLSin_ACcouple1.1
unnamed: DigitalOut1.2, SpdifOut_ImpedanceMatch1.2
unnamed: LLS In1.4 (B), LLSin_ACcouple1.2
unnamed: LLS Out1.4 (B), SpdifOut_AcCoupling1.1
unnamed: SpdifOut_AcCoupling1.2, SpdifOut_ImpedanceMatch1.1
VCCQ: RAM1.3 (VDDQ_1), RAM1.9 (VDDQ_2), RAM1.43 (VDDQ_3), RAM1.49 (VDDQ_4)
VDD: ADC1.6 (VD), ADC1.14 (DIF/TDMI), C6.1, C7.2, DAC1.4 (MUTEB), DAC1.9 (VDDB), DacAnalogSupply_bead1.1, Dac_ChargePump_bead1.1, Dac_DigitalSup_bulk2.1, Dac_DigitalSup_noise2.1, FLASH1.12 (VCC_1), FLASH1.37 (VCC_2), LLS Out1.1 (VCCA), LLS Out1.5 (DIR), RAM1.1 (VDD_1), RAM1.14 (VDD_2), RAM1.27 (VDD_3), SPDIFTX1.22 (DVDD), SPDIFTX1.34 (RST), VdivHigh1.1, adcBead1.1, adcReset_rc_cap1.1, adcReset_rc_res1.2, adc_dSupply_bulk1.1, adc_dSupply_noise1.1, dixSupply_bulk1.1, dixSupply_noise1.1, llsOut_refHi_noise2.2
VDDA: C4.1, C5.2, LLS In1.1 (VCCA), llsOut_refHi_noise1.2
VDD_DIV: LLS In1.6 (VCCB), LLS Out1.6 (VCCB), VdivHigh1.2, VdivLow1.1, llsOut_refLo_noise1.1, llsOut_refLo_noise2.1

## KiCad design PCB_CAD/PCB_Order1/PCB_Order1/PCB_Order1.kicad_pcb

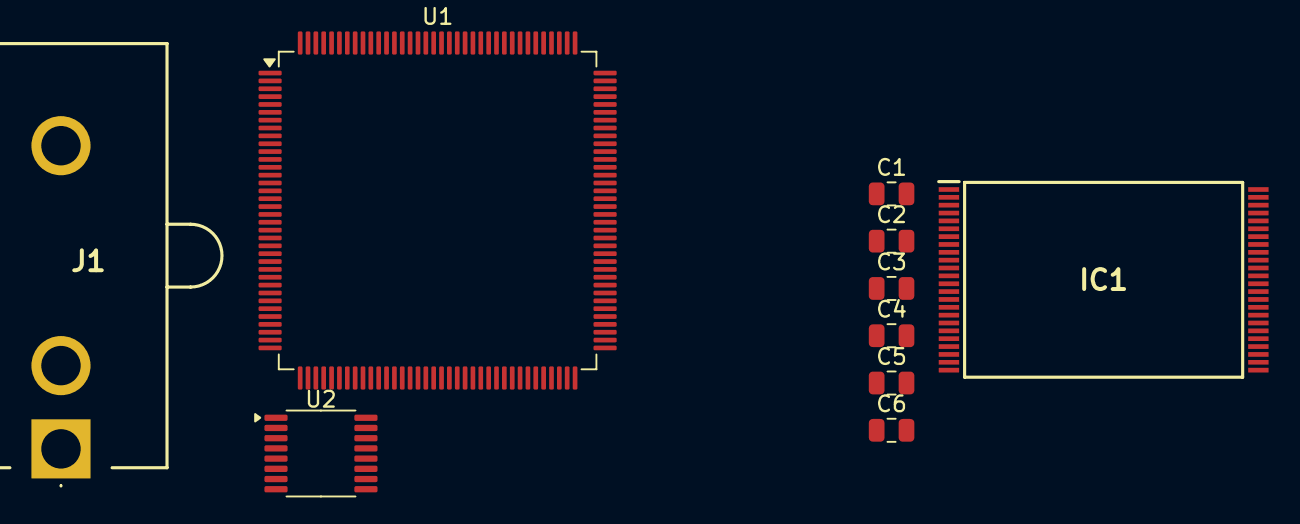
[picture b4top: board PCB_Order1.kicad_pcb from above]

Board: 2 copper layers, 10 parts (0 on the bottom side), 24 nets, no tracks yet.

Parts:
C1: .47u; C_0805_2012Metric
C2: 1u; C_0805_2012Metric
C3, C5: .1u; C_0805_2012Metric
C4, C6: 10u; C_0805_2012Metric
IC1: TC58BVG1S3HTA00; SOP50P2000X120-48N
J1: FW6190
U1: STM32H7A3ZITx; LQFP-144_20x20mm_P0.5mm
U2: AK5720VT; TSSOP-16_4.4x5mm_P0.65mm

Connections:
/Flash_CE: IC1.9 (~CE), U1.98 (PC8)
/Flash_CLE: IC1.16 (CLE), U1.81 (PD12)
/Flash_IO1: IC1.29 (I/O1), U1.85 (PD14)
/Flash_IO2: IC1.30 (I/O2), U1.86 (PD15)
/Flash_IO3: IC1.31 (I/O3), U1.114 (PD0)
/Flash_IO4: IC1.32 (I/O4), U1.115 (PD1)
/Flash_IO5: IC1.41 (I/O5), U1.58 (PE7)
/Flash_IO6: IC1.42 (I/O6), U1.59 (PE8)
/Flash_IO7: IC1.43 (I/O7), U1.60 (PE9)
/Flash_IO8: IC1.44 (I/O8), U1.63 (PE10)
/Flash_RE: IC1.8 (~RE), U1.118 (PD4)
/Flash_WE: IC1.18 (~WE), U1.119 (PD5)
/I2S1_CK: U1.41 (PA5), U2.12 (BICK)
/I2S1_MCK: U1.44 (PC4), U2.11 (MCLK)
/I2S1_SDI: U1.42 (PA6), U2.9 (SDTO)
/I2S1_WS: U1.110 (PA15), U2.10 (LRCLK)
GND: C1.2, C2.2, C3.1, C4.2, C5.2, C6.2, J1.1, U2.4 (VSS), U2.15 (FSEL), U2.16 (CKS)
unnamed: U1.16 (VSS), U1.38 (VSS), U1.51 (VSS), U1.61 (VSS), U1.83 (VSS), U1.94 (VSS), U1.107 (VSS), U1.120 (VSS), U1.130 (VSS)
unnamed: C5.1, C6.1, U2.6 (VD), U2.7 (GSEL)
unnamed: J1.3, U2.3 (LIN)
unnamed: C2.1, U2.8 (REGO)
unnamed: J1.2, U2.2 (RIN)
unnamed: C3.2, C4.1, U2.5 (VA)
unnamed: C1.1, U2.1 (VCOM)

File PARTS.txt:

microcontroller
STM32H7A3ZIT6
https://www.digikey.com/en/products/detail/stmicroelectronic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
$15.22
This is the microcontroller in our dev board. A -Q version with internal SMPS is also available. ST says this is not necessarily unless hyper-optimizing power efficiency, see here: https://community.st.com/t5/stm32-mcus-boards-and-hardware/s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

ADC
AKM AK5720VT
https://www.digikey.com/en/products/detail/asahi-kasei-micro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
$2.71
Cheapest option on Digikey for filters "audio ADC," "2 channels," "I2S." Nothing in the datasheet to indicate it wouldn't be able to meet spec based on my limited understanding. More expensive options are mostly from TI, main differentiating factor seems to be higher sampling rate and/or more bit depth, but 96k/24b is already excessive for our purposes.

DAC
Cirrus WM8524CGEDT
https://www.digikey.com/en/products/detail/cirrus-logic-inc/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
$2.62
Used same initial selection parameters as for ADC, a lot more options than in that category. To narrow down further seemed intuitive to elect a DAC around the same price and in the same package format as the ADC already elected (although DACs seem cheaper than ADCs for the same specifications). Saw nothing concerning in datasheet. Other ADCs in the same price bracket are mostly made by TI, hard to differentiate between so many similar models

Stereo RCA jack
Cliff FW6190
https://www.digikey.com/en/products/detail/cliff-electronic-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
2 x $2.62 (input & output) = $5.24
Two options (in stock & shipping) on Digikey for color-coded stereo left & right in one package, one is right-angle, one is straight-thru. Straight-thru seems cooler if the board is exposed anyway and the price is similar

Toslink RX
Toshiba TORX1950A(F)
https://www.mouser.com/ProductDetail/Toshiba/TORX1950AF?qs=g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
$13.83
For this and Toslink tx — the market is hard. Toshiba also makes rx/tx that allow you to attach your own LED drive instead of having it built into the receptacle module, but they appear to have been obsoleted or to be on unsustainably long lead times. I'd like vertical-facing for parity with the RCA jacks but that similarly appears to be unobtainium. "A" in the product name means LED drive integrated, I don't know what "F" means, and there would be "V" if it was vertical-facing. The 1950A tx/rx will work for the moment and I will look further into trying to source some without integrated LED drive later on if I have time.
Also: Digikey doesn't sell the 1950 tx/rx, only Mouser does.

Toslink TX
Toshiba TOTX1950A(F)
https://www.mouser.com/ProductDetail/Toshiba/TOTX1950AF?qs=g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
$14.76
Reasoning see above

New design assumption -> No supplemental flash, do everything in RAM. Easier way to meet minimal spec.
Problem: Largest SDRAM chip available is only 512 Mbit, at least based upon filtered Digikey search and a Stackexchange post we found from 2018 (post here: https://electronics.stackexchange.com/questions/397458/stm32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 In our feasibility study we thought that we would need around 900 Mbit JUST for storage of audio clips if assuming CD standard (stereo, 44.1 ksps, 16 bit depth).
Some observations:
Smallest available package for 512 Mbit (or 256 Mbit) is 54 pins. This necessitates MINIMALLY 108 pins hooked up for CD standard audio (and leaving only around 100 Mbit margin of error / overhead is probably not smart).
512 Mbit packages are really expensive per actual bit. 256 Mbit packages are cheaper but this only amplifies the "that's a Lot of pins to hook up" problem.
At least 44.1 ksps is necessary to meet spec for frequency response (Shannon-Nyquist theorem) but nothing was formally specified about bit depth. 16 bits depth is almost certainly overkill considering that everything analog in the circuit is going to be (relatively) noisy, and also, SNR was not formally specified. I think we could get away with possibly as little as 10 bits depth although I need to get an actual formula for bit depth<->dynamic range to assess this more confidently. Finally, stereo audio was not formally specified, mono would minimally meet spec.
We are going to have to hook up AT LEAST one 54-pin RAM pad any way, any how. The question then becomes, is the tradeoff acceptable to avoid doing two. Would two even be feasible at all? Is there any universe where we have the PCB design chops to make that happen? Wouldn't that be a huge pain in the neck given the actual scope of our project and our current priors?
I'm going to make a wild guess that the (comparatively) nominal per-bit cost savings from buying 256 Mbit pads DOES NOT outweigh the enormous pain in the neck it would be to actually hook that up

Power supply selection observations: It would be most convenient if we could fire everything off one voltage and did not need to elect a multiple-output unit (for the prebuilt PSU case). µcontroller and RAM chip(s) have non-negligible consumption, I think everything else has negligible consumption. With a single RAM chip and the H7A3ZIT6 could we get away with a 1 W supply? 1.5 W?

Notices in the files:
CubeMX_STM32H7A3ZIT/Core/Src/fmc.c:
Copyright (c) 2024 STMicroelectronics.
All rights reserved.
This software is licensed under terms that can be found in the LICENSE file
